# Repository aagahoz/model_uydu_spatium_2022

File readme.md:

Proje geliştirme aşamaları ve Programlama konularında oldukça tecrübe kazandıran, 2 sene #GömülüSistemGeliştiricisi ve Takım Kaptanı olarak görev aldığım, geçtiğimiz yıl #Finalist olarak yarıştığımız, Türksat-Teknofest #ModelUyduYarışması 2022 için yaptığımız tüm geliştirmeleri aşağıdaki repoda paylaşmaktayım.
#ESP32, #RaspberryPi Zero, #Arduino gibi mikroişlemciler kullandığımız projemizde #FreeRTOS gibi yapılar da kullandık.

- ESP32 çift yönlü WiFi ve LoRa ile Yer İstasyonu haberleşmesi
- ESP32 - Arduino arasında UART telemetri aktarımı ( data parsing )
- ESP32 ve Raspberry Pi ile çift yönlü UART data aktarımı
- ESP32 ve ESP32 arasında LoRa telemetri aktarımı
- Raspberry Pi ile Pixhawk haberleşmesi
- Raspberry Pi - Yer İstasyonu arası TCP Dosya Aktarımı
- ESP32 ile BMP280, Voltage Divider, RTC Okuması ( I2C BUS )
- ESP32 ile SD Card Telemetri kaydedilmesi
- Gazebo ile uçuş simulasyonu yapılması
- Görev yükü ve Taşıyıcı için PCB tasarımları

Repo fazlasıyla düzensiz şuan maalesef. Vakit bulamadığım için düzenleyemedim. Repo hakkında veya yarışma hakkında sorularınız için her zaman iletişime geçebilirsiniz.

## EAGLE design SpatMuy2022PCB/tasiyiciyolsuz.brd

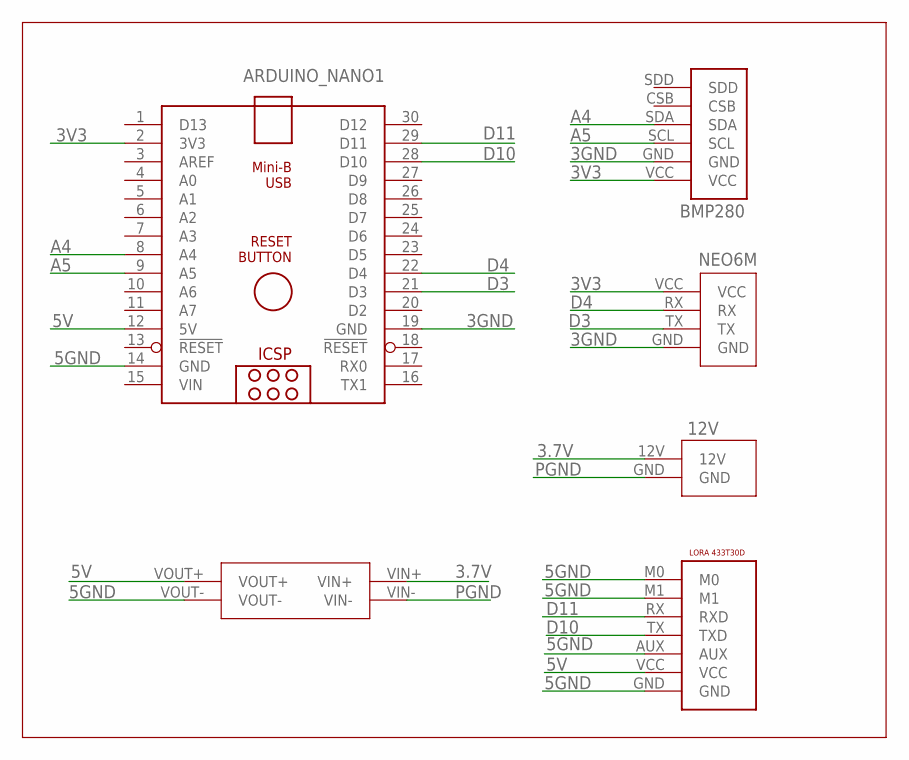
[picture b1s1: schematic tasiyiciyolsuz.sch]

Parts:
ARDUINO_NANO1: ARDUINO_NANO
BMP1: BMP280
U$1: 12V
U$2: LORAFULLSIZE
U$3: MT3608_REGULATOR
U$4: NEO6M

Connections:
3.7V: U$1.12V, U$3.VIN+
3GND: ARDUINO_NANO1.19 (GND), BMP1.GND, U$4.GND
3V3: ARDUINO_NANO1.2 (3V3), BMP1.VCC, U$4.VCC
5GND: ARDUINO_NANO1.14 (GND), U$2.AUX, U$2.GND, U$2.M0, U$2.M1, U$3.VOUT-
5V: ARDUINO_NANO1.12 (5V), U$2.VCC, U$3.VOUT+
A4: ARDUINO_NANO1.8 (A4), BMP1.SDA
A5: ARDUINO_NANO1.9 (A5), BMP1.SCL
D3: ARDUINO_NANO1.21 (D3), U$4.TX
D4: ARDUINO_NANO1.22 (D4), U$4.RX
D10: ARDUINO_NANO1.28 (D10), U$2.TX (TXD)
D11: ARDUINO_NANO1.29 (D11), U$2.RX (RXD)
PGND: U$1.GND, U$3.VIN-
VIN: ARDUINO_NANO1.15 (VIN)

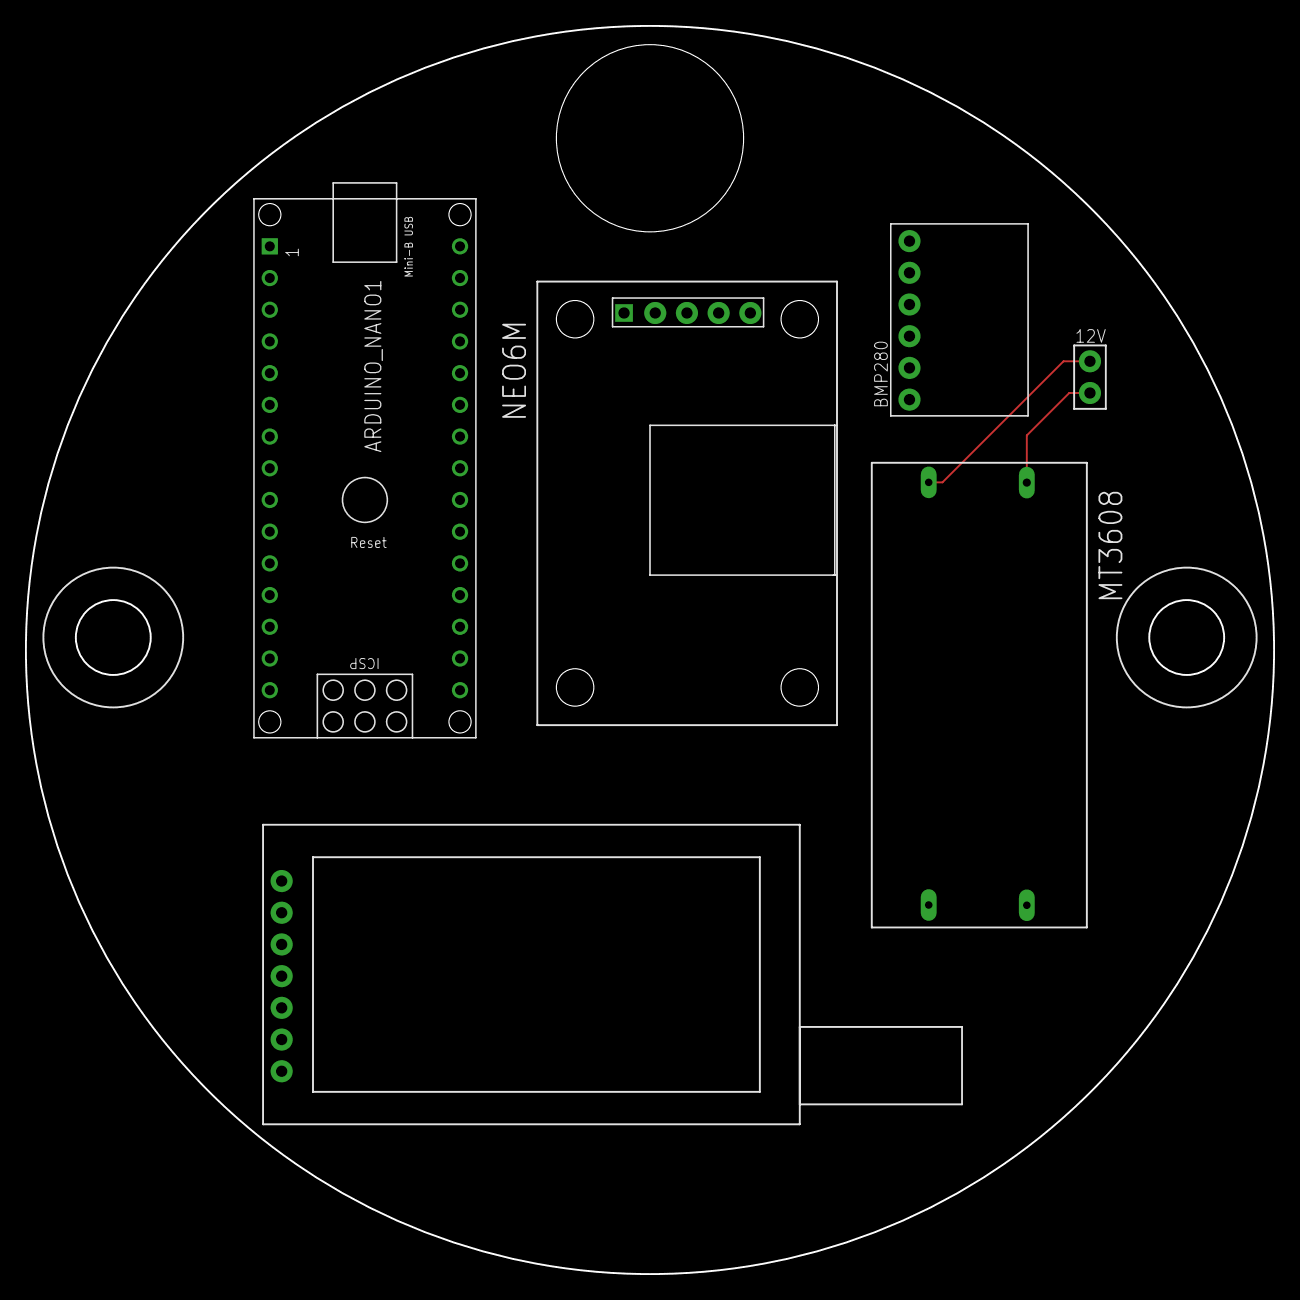
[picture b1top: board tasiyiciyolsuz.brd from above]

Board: 2 copper layers, 100.0 x 100.0 mm, 6 parts (0 on the bottom side), 12 nets.

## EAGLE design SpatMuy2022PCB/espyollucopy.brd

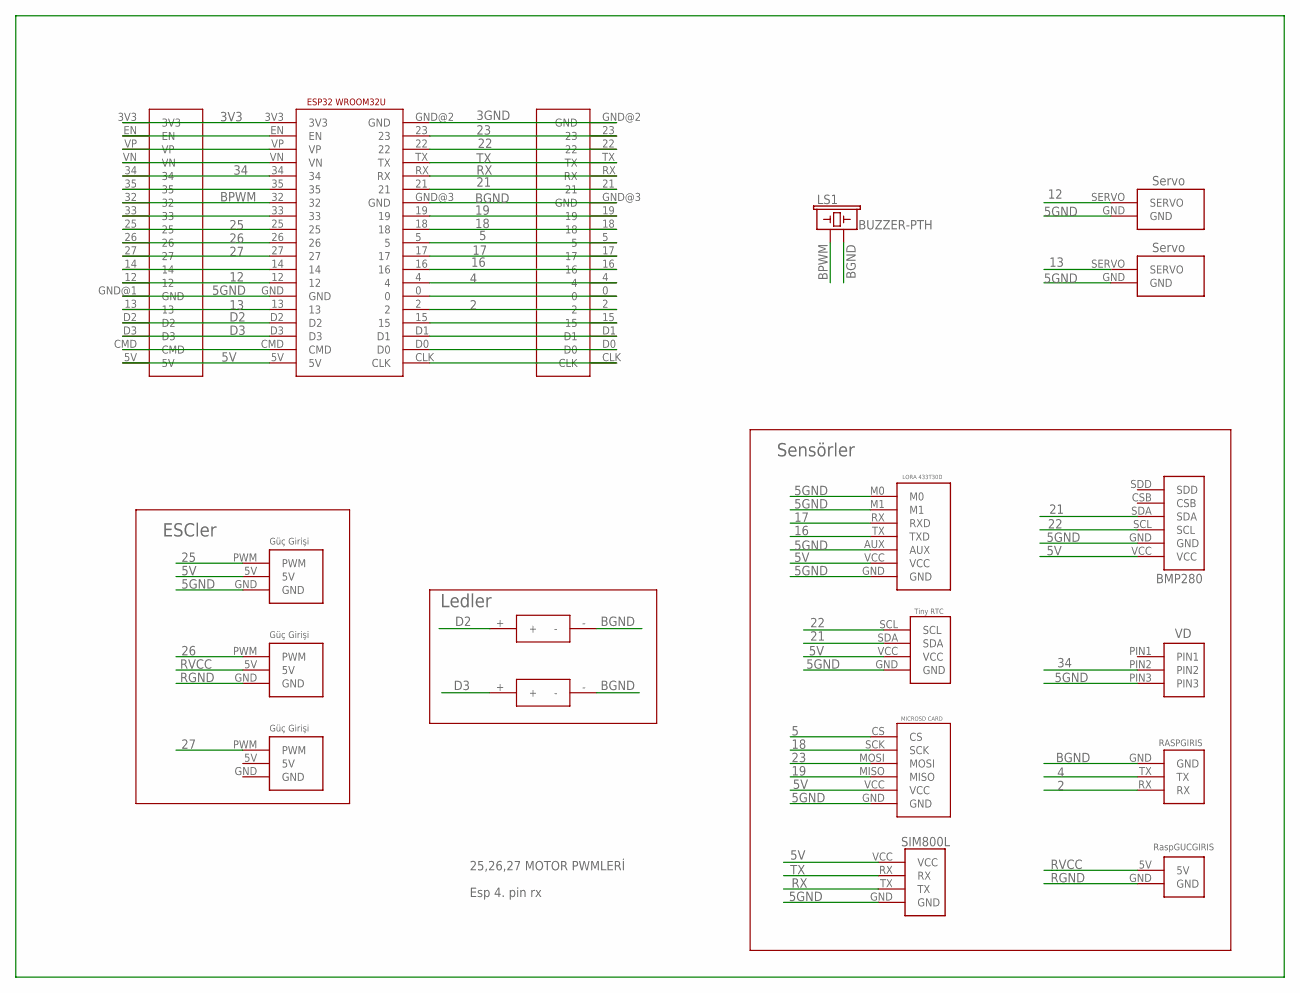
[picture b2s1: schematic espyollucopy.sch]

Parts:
BMP1: BMP280
LS1: BUZZER-PTH; BUZZER-12MM
U$1: TINYRTC
U$2: VOLTAGE_DIVIDER
U$3: RASPGIRIS
U$4: ESP32WROOM32U
U$5: LORAFULLSIZE
U$6: MICROSD_CARD
U$7, U$9: SERVO_SIGNAL
U$8: SIM800L
U$10: RASPGUCGIRIS
U$11, U$12, U$13: ESC_GIRIS
U$14: ESPSAGPIN
U$15: ESPSOLPIN
U$17, U$18: LED

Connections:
2: U$3.RX, U$4.2, U$14.2
3GND: U$4.GND@2 (GND), U$14.GND@2 (GND)
3V3: U$4.3V3, U$15.3V3
4: U$3.TX, U$4.4, U$14.4
5: U$4.5, U$6.CS, U$14.5
5GND: BMP1.GND, U$1.GND, U$2.PIN3, U$4.GND, U$5.AUX, U$5.GND, U$5.M0, U$5.M1, U$6.GND, U$7.GND, U$8.GND, U$9.GND, U$11.GND, U$15.GND@1 (GND)
5V: BMP1.VCC, U$1.VCC, U$4.5V, U$5.VCC, U$6.VCC, U$8.VCC, U$11.5V, U$15.5V
12: U$4.12, U$7.SERVO, U$15.12
13: U$4.13, U$9.SERVO, U$15.13
16: U$4.16, U$5.TX (TXD), U$14.16
17: U$4.17, U$5.RX (RXD), U$14.17
18: U$4.18, U$6.SCK, U$14.18
19: U$4.19, U$6.MISO, U$14.19
21: BMP1.SDA, U$1.SDA, U$4.21, U$14.21
22: BMP1.SCL, U$1.SCL, U$4.22, U$14.22
23: U$4.23, U$6.MOSI, U$14.23
25: U$4.25, U$11.PWM, U$15.25
26: U$4.26, U$12.PWM, U$15.26
27: U$4.27, U$13.PWM, U$15.27
34: U$2.PIN2, U$4.34, U$15.34
BGND: LS1.- (2), U$3.GND, U$4.GND@3 (GND), U$14.GND@3 (GND), U$17.-, U$18.-
BPWM: LS1.+ (1), U$4.32, U$15.32
D2: U$4.D2, U$15.D2, U$17.+
D3: U$4.D3, U$15.D3, U$18.+
unnamed: U$4.EN, U$15.EN
unnamed: U$4.VP, U$15.VP
unnamed: U$4.VN, U$15.VN
unnamed: U$4.35, U$15.35
unnamed: U$4.33, U$15.33
unnamed: U$4.14, U$15.14
unnamed: U$4.CMD, U$15.CMD
unnamed: U$4.0, U$14.0
unnamed: U$4.15, U$14.15
unnamed: U$4.D1, U$14.D1
unnamed: U$4.D0, U$14.D0
unnamed: U$4.CLK, U$14.CLK
RGND: U$10.GND, U$12.GND
RVCC: U$10.5V, U$12.5V
RX: U$4.RX, U$8.TX, U$14.RX
TX: U$4.TX, U$8.RX, U$14.TX

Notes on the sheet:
Ledler
ESCler
Sensörler
25,26,27 MOTOR PWMLERİ
Esp 4. pin rx

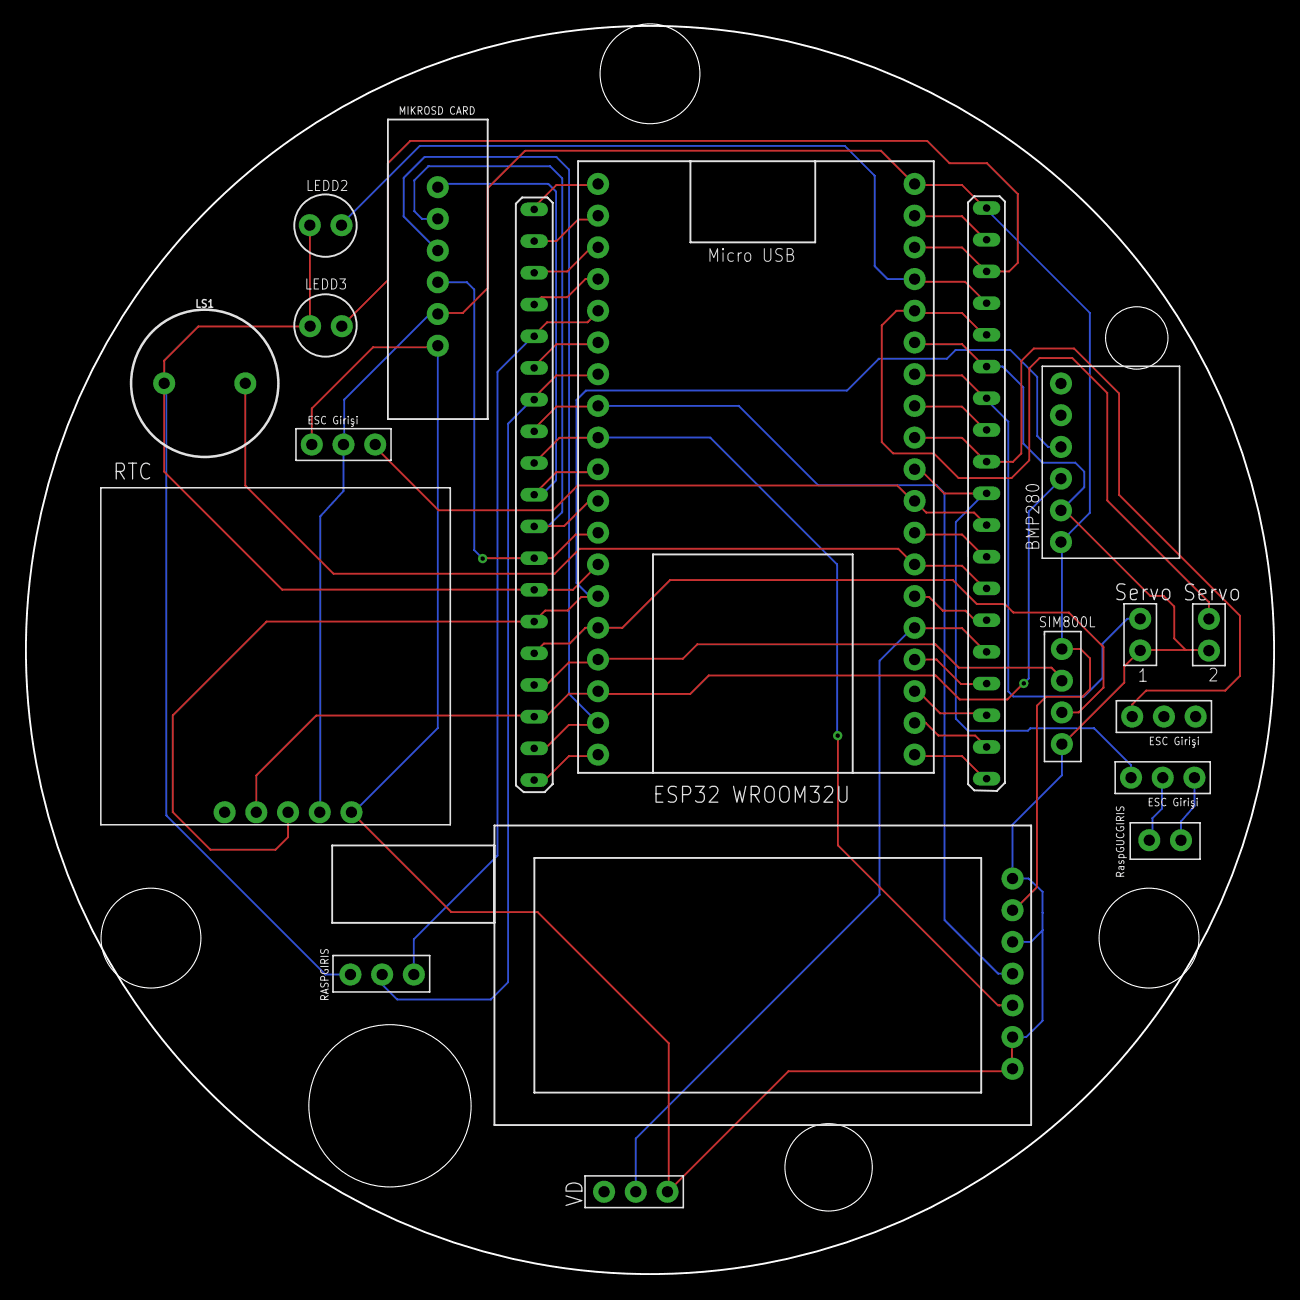
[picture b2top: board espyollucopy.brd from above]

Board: 2 copper layers, 100.0 x 100.0 mm, 19 parts (0 on the bottom side), 40 nets.

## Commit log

2022-06-19 Telemetri Communication and Servo Control
    Cift yonlu wifi haberlesmesi ve manuel servo motor kontrol eklendi
2022-06-19 Add files via upload
    RTC okuma eklendi
    Kod aciklamalari eklendi
2022-06-19 Add files via upload
    Telemetri degiskenleri eklendi
    Iyilestirmeler yapildi
2022-06-19 Add files via upload
    /*
    * BMP280 Okuma +
    * GPS Okuma +
    * LoRa Haberlesme -
    */
2022-06-19 Add files via upload
    /*
    * telemetri gonderimi +
    * komut gonderimi +
    * dosya aktarımı -
    * servo motor kontrol +
    * analog okuma -
2022-06-19 Add files via upload
    /*
    * LoRa Receiver -
    * BMP280 +
    * Raspberry Pi UART -
    */
2022-06-19 Add files via upload
    # ESP32 UART -
    # PixHawk Motor -
    # PixHawk IMU Okuma -
    # PixHawk GPS Okuma -
    # Goruntu Isleme -
2022-06-19 Add files via upload
    Pin Bağlantıları
2022-06-23 Add files via upload
    QR için planlanan tasarım
2022-07-02 komutlar
2022-07-02 hatalar giderildi
2022-07-03 lora eklendi
2022-07-03 sistemsel olarak bitti
2022-07-03 Esranın taşıyıcı kodu
2022-07-11 Add files via upload
    tüm veriler eklendi.
2022-07-11 voltage divider code
2022-07-12 Yer İstasyonu 14.0
2022-07-13 Raspberry Pi UART Transmit Eklendi
2022-07-13 SD kart eklendi
2022-07-14 Servo Motor Kontrol Eklendi
2022-07-14 Manuel Tahrik Eklendi
2022-07-16 UDP haberleşme güncellemeleri yapıldı
2022-07-18 olduuu
2022-08-02 Add files via upload
    Simülasyon için basit komutlar
2022-08-13 Sensor Okuma ve Uart Gonderimi
    Dronekit ile IMU ve GPS okumalari ve UART uzerinden esp32 ye gonderimi
2022-08-22 Create Yer istasyonu
    Güncel versiyon
2022-08-22 Yer istasyonu güncellendi
    Güncel versiyon
2022-08-22 Create Yer istasyonu
2022-08-22 Yer istasyonu güncellendi
    son sürüm

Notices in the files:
parts and their libraries:
SparkFun-Electromechanical: Licensing: Creative Commons ShareAlike 4.0 International - https://creativecommons.org/licenses/by-sa/4.0
